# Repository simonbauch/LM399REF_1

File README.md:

# LM399REF_1
A basic LM399 based reference board.
More Info: https://db4uch.de/2025/02/02/a-basic-lm399-adr1399-based-10v-reference/

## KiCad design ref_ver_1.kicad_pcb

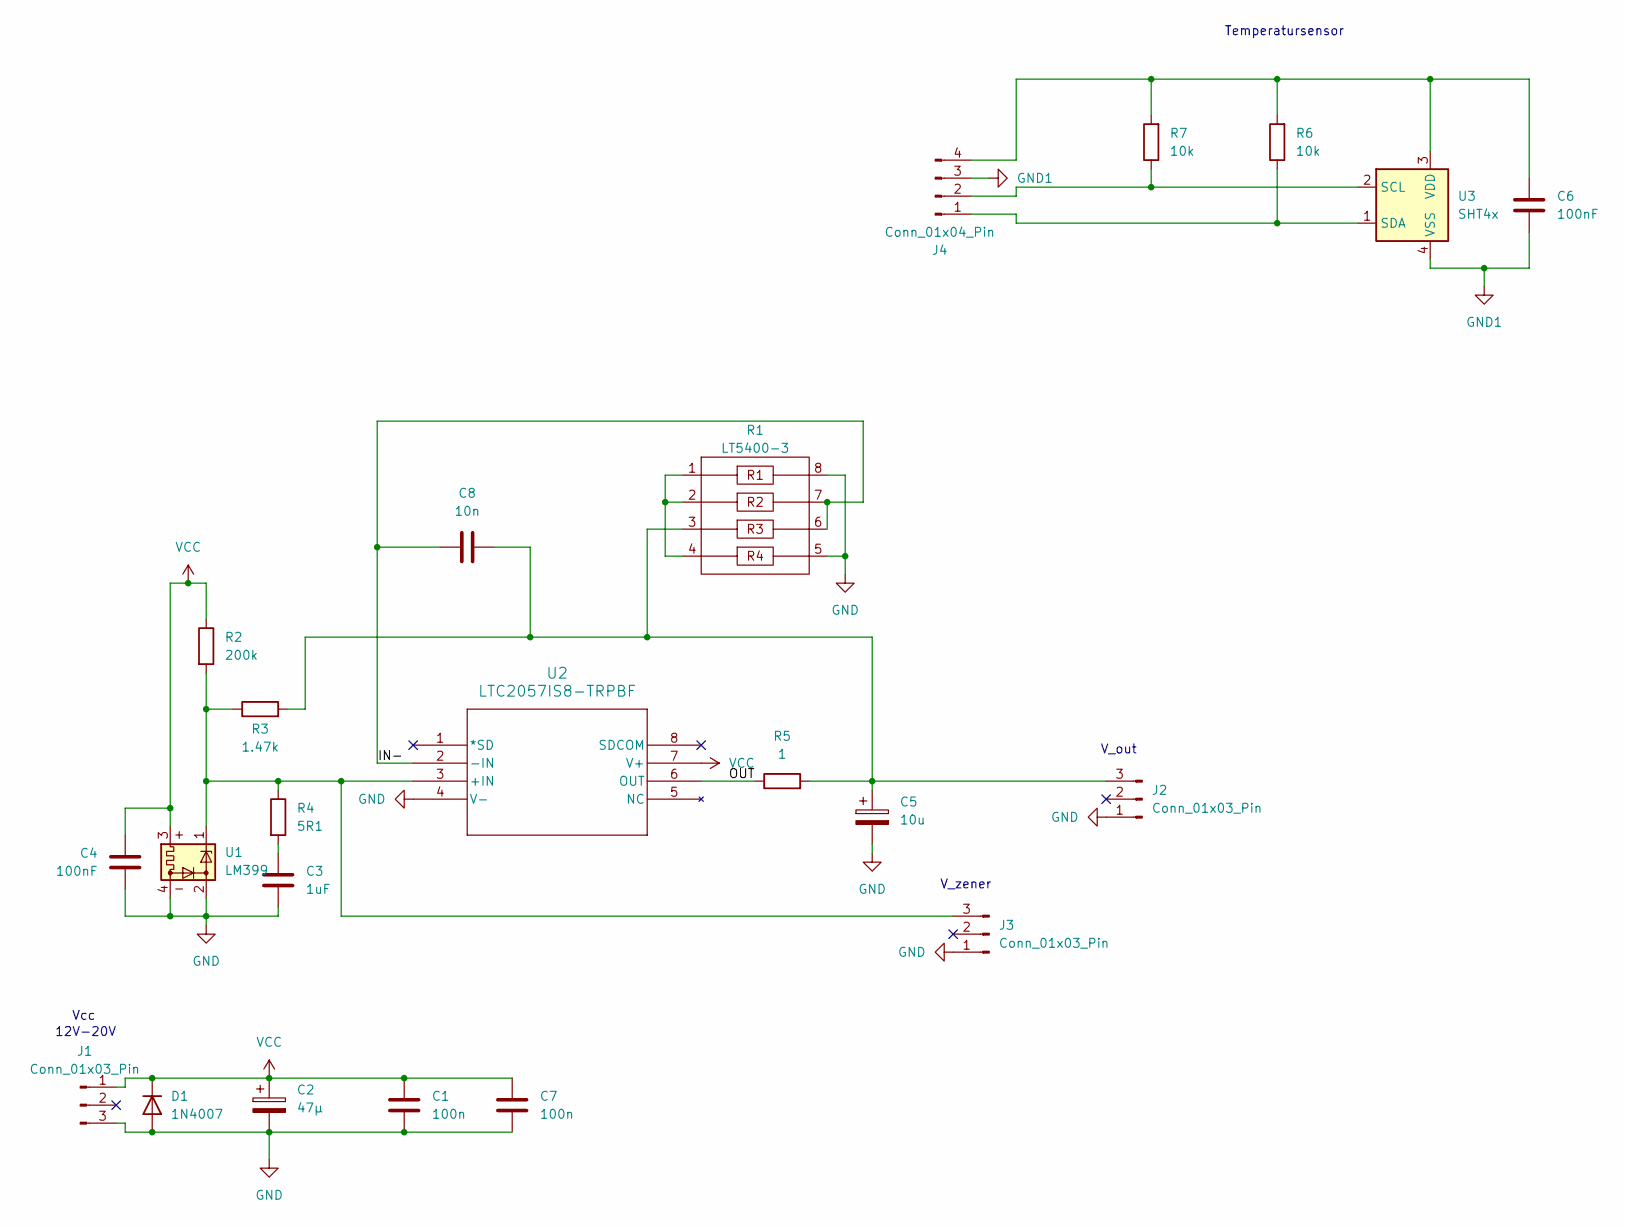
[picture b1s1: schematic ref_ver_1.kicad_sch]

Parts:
C1, C7: 100n; C_0603_1608Metric_Pad1.08x0.95mm_HandSolder
C2: 47µ; CAPAE660X600N
C3: 1uF; C_0603_1608Metric_Pad1.08x0.95mm_HandSolder
C4, C6: 100nF; C_0603_1608Metric_Pad1.08x0.95mm_HandSolder
C5: 10u; CP_EIA-6032-15_Kemet-U_Pad2.25x2.35mm_HandSolder
C8: 10n; C_0603_1608Metric_Pad1.08x0.95mm_HandSolder
D1: 1N4007; D_DO-41_SOD81_P10.16mm_Horizontal
J1, J2, J3: Conn_01x03_Pin; FanPinHeader_1x03_P2.54mm_Vertical
J4: Conn_01x04_Pin; PinHeader_1x04_P2.54mm_Vertical
R1: LT5400-3; MSOP-8_MS_LIT-M
R2: 200k; R_Axial_DIN0207_L6.3mm_D2.5mm_P7.62mm_Horizontal
R3: 1.47k; R_Axial_DIN0207_L6.3mm_D2.5mm_P7.62mm_Horizontal
R4: 5R1; R_0603_1608Metric_Pad0.98x0.95mm_HandSolder
R5: 1; R_0603_1608Metric_Pad0.98x0.95mm_HandSolder
R6, R7: 10k; R_0603_1608Metric_Pad0.98x0.95mm_HandSolder
U1: LM399; Analog_TO-46-4_ThermalShield
U2: LTC2057IS8-TRPBF; SO-8_S_LIT-M
U3: SHT4x; Sensirion_DFN-4_1.5x1.5mm_P0.8mm_SHT4x_NoCentralPad

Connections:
/IN-: C8.1, R1.6, R1.7, U2.2 (-IN)
/OUT: R5.1, U2.6 (OUT)
GND: C1.2, C2.2, C3.2, C4.1, C5.2, C7.2, D1.2 (A), J1.3, J2.1, J3.1, R1.5, R1.8, U1.2, U1.4, U2.4 (V-)
GND1: C6.1, J4.3, U3.4 (VSS)
unnamed: C3.1, R4.2
unnamed: C5.1, C8.2, J2.3, R1.3, R3.2, R5.2
unnamed: J3.3, R2.2, R3.1, R4.1, U1.1, U2.3 (+IN)
unnamed: J4.1, R6.1, U3.1 (SDA)
unnamed: J4.2, R7.1, U3.2 (SCL)
unnamed: C6.2, J4.4, R6.2, R7.2, U3.3 (VDD)
unnamed: R1.1, R1.2, R1.4
VCC: C1.1, C2.1, C4.2, C7.1, D1.1 (K), J1.1, R2.1, U1.3, U2.7 (V+)

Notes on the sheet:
V_zener
V_out
Vcc
Temperatursensor
12V-20V

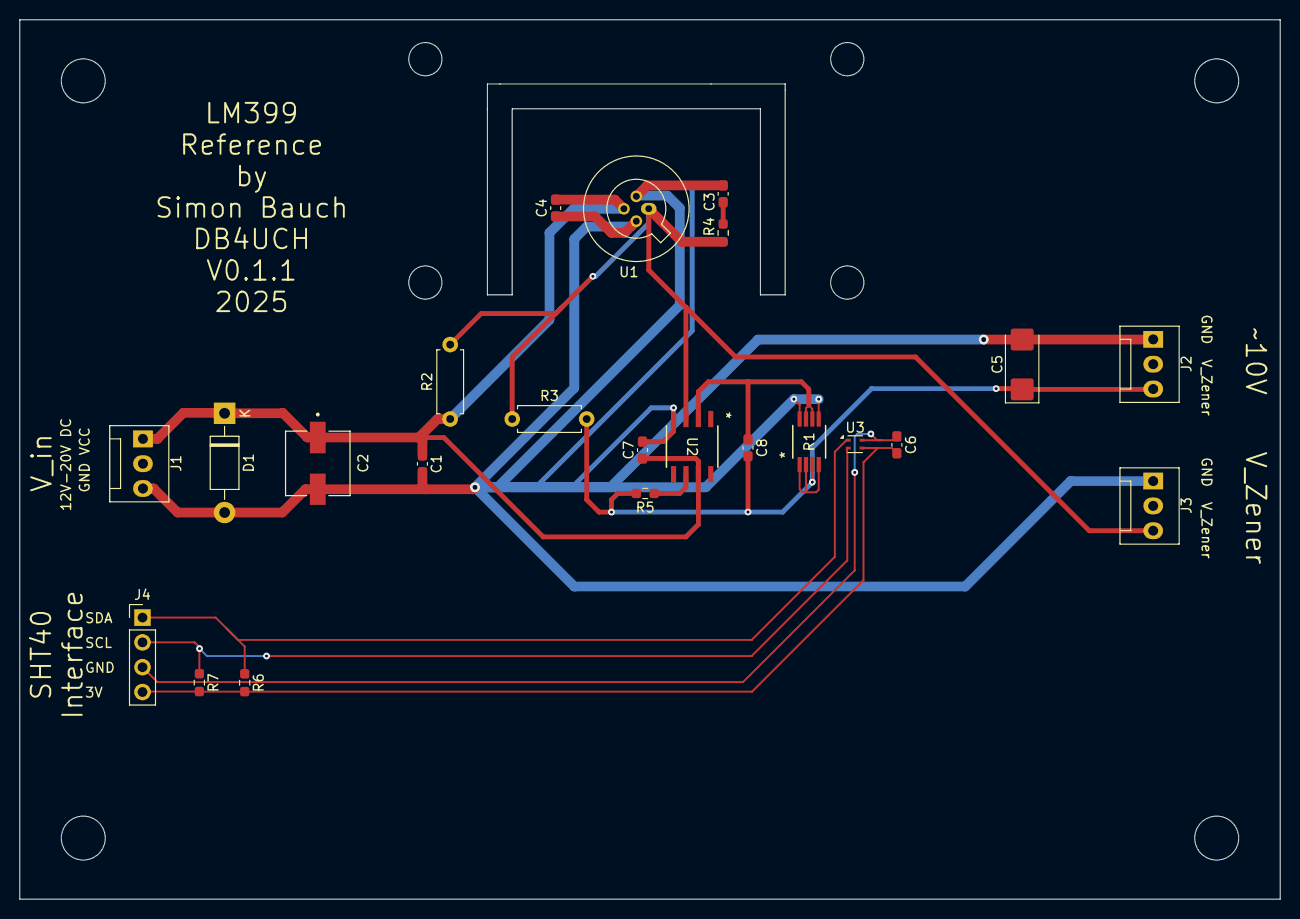
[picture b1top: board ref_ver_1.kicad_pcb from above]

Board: 2 copper layers, 128.9 x 89.9 mm, 23 parts (0 on the bottom side), 12 nets.

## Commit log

2025-02-02 Create test
2025-02-02 updated to new revision
2025-02-03 Small changes to the PCB before production
